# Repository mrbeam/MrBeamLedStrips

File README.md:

# MrBeamLedStrips

MrBeamLedStrips is a standalone component that handles Mr Beam II's LED strips.

## Usage
#### Socket Connection
There is a socket: `/var/run/mrbeam_ledstrips.sock`

Currently MrBeamPlugin does not use the socket connection. 
Still this needs to be done for performance! Some day...

#### Command Line Interface (CLI)
Or use the command line interface:
* `mrbeam_ledstrips_cli [command]`  Commands:

    * `` (no command) Prints version of MrBeamLedStrips. (Does not connect to daemon.)
    * `?` Prints version, list of possible commands and debug information
    * `unknown`
    * `DebugStop`  # breaks -> SW-1733
    * `on`, `all_on`
    * `off`, `all_off`
    * `brightness` # Error
    * `rollback`
    * `fps` # Error
    * `spread_spectrum` # Error
    * `ignore_next_command`
    * `ignore_stop`
    * `Listening`, `_listening`, `listening`
    * `Startup`
    * `ClientOpened`
    * `ClientClosed`
    * `Error`
    * `Shutdown`
    * `ShutdownPrepare`
    * `ShutdownPrepareCancel`
    * `Upload`
    * `PrintStarted`
    * `PrintDone`
    * `PrintCancelled`
    * `PrintPaused`
    * `PrintPausedTimeout`
    * `PrintPausedTimeoutBlock`
    * `ButtonPressReject`
    * `PrintResumed`
    * `Progress:<progress>`, `progress:<progress>`
    * `JobFinished`, `job_finished`
    * `Pause`, `pause`
    * `ReadyToPrint`
    * `ReadyToPrintCancel`
    * `SlicingStarted`
    * `SlicingDone`
    * `SlicingCancelled`
    * `SlicingFailed`
    * `SlicingProgress:<progress>`, `slicing_progress:<progress>`
    * `SettingsUpdated`  # breaks -> SW-1733
    * `LaserJobDone`
    * `LaserJobCancelled`
    * `LaserJobFailed`
    * `white`, `all_white`
    * `red`, `all_red`
    * `green`, `all_green`
    * `blue`, `all_blue`
    * `yellow`, `all_yellow`
    * `orange`, `all_orange`

## Config
For configuration see:
 * `iobeam/extras/mrbeam_ledstrips.yaml` or 
 * `/etc/mrbeam_ledstrips.yaml` after deployment.

## Change Log

##### 0.1.11
New commands:
* Command `ButtonPressReject`: Intended to give feedback that a button press is an invalid action at the moment. 
Flashes red once and the rolls back.
* README.md added
##### < 0.1.10
See commit log

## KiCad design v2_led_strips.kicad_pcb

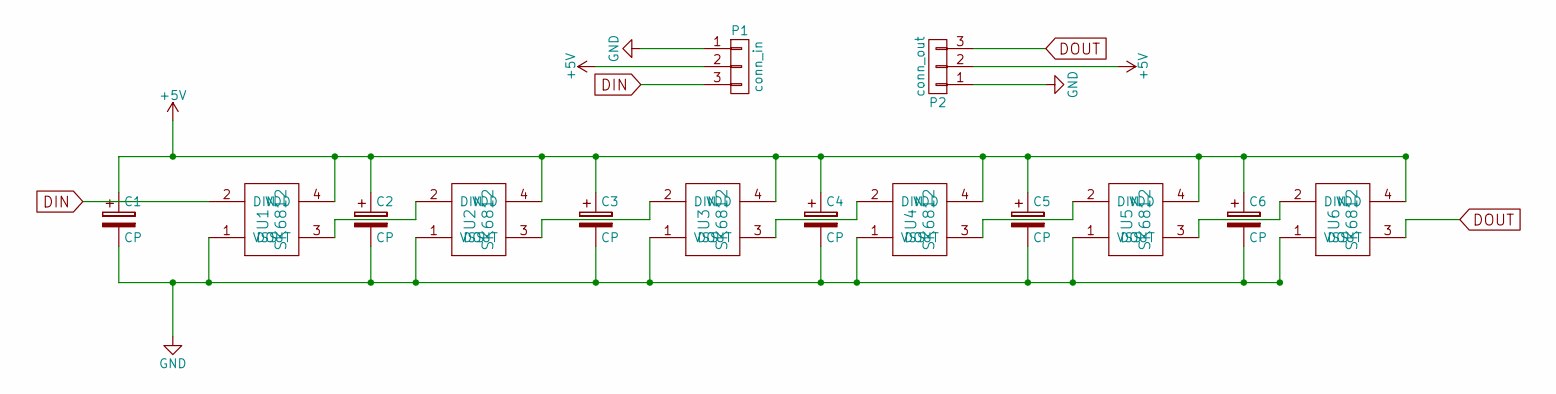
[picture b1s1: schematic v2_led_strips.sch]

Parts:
C1, C2, C3, C4, C5, C6: CP; C_1206
P1: conn_in; GS3
P2: conn_out; GS3
U1, U2, U3, U4, U5, U6: SK6812; PLCC4-5050

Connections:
+5V: C1.1, C2.1, C3.1, C4.1, C5.1, C6.1, P1.2, P2.2, U1.4 (VDD), U2.4 (VDD), U3.4 (VDD), U4.4 (VDD), U5.4 (VDD), U6.4 (VDD)
DIN: P1.3, U1.2 (DIN)
DOUT: P2.3, U6.3 (DOUT)
GND: C1.2, C2.2, C3.2, C4.2, C5.2, C6.2, P1.1, P2.1, U1.1 (VSS), U2.1 (VSS), U3.1 (VSS), U4.1 (VSS), U5.1 (VSS), U6.1 (VSS)
unnamed: U1.3 (DOUT), U2.2 (DIN)
unnamed: U2.3 (DOUT), U3.2 (DIN)
unnamed: U3.3 (DOUT), U4.2 (DIN)
unnamed: U4.3 (DOUT), U5.2 (DIN)
unnamed: U5.3 (DOUT), U6.2 (DIN)

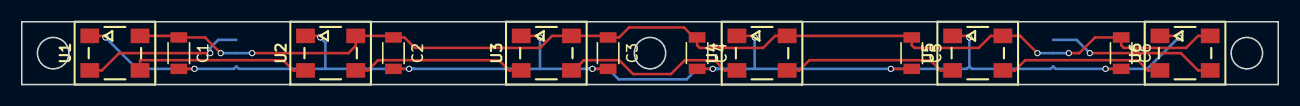
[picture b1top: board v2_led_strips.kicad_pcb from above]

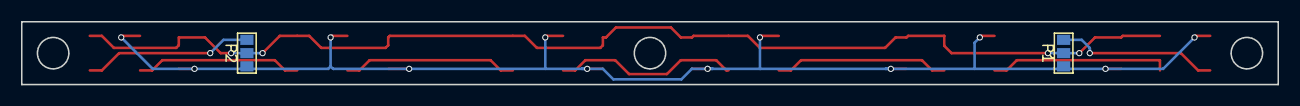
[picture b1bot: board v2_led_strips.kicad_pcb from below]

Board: 2 copper layers, 120.0 x 6.0 mm, 14 parts (2 on the bottom side), 9 nets.

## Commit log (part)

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2016-05-30 initial commit v2 led strips. work in progress.
2016-09-07 reusing this repo for LEDs software dev. initial commit
2016-09-07 added src folder
2016-09-07 color definitions
2016-09-07 fixed progress 100% value
2016-09-07 reading state from socket
2016-09-08 work in progress
2016-09-09 bugfix.
2016-09-09 added ws281x lib
2016-09-10 cli for chatting with socket
2016-09-10 wip: added installer
2016-09-10 move did not work.
2016-09-10 renamed package
2016-09-10 package init file and versioneer file
2016-09-10 import fixes
2016-09-10 cleaner structure
2016-09-10 removed rpi_ws281x code as there is already a python package
2016-09-10 added config exception
2016-09-10 fetch config from file
2016-09-10 fixed imports
2016-09-10 better fail messages
2016-09-10 pid-file is handled by daemon - not by init script.
2016-09-11 added unit file for systemd based distributions
2016-09-19 slower clientOpened connection
2016-10-10 added all_on state for power measurements
2016-10-10 fixed indentation
2016-10-20 bugfix. indentations.
2016-10-20 bugfix - unit files have extension .service
2017-01-12 added pycharm project folder to to .gitignore
2017-01-13 fixed spacing
2017-01-13 fixed a lot of spacing and semicolon stuff
2017-01-17 initial commit of update bash script.
2017-01-17 added uninstall and install to update script.
2017-01-17 fixed naming error.
2017-01-17 added "don't ask for confirmation" option to uninstall command
2017-01-23 added line to test software update.
2017-01-23 fixed typo in systemctl restart command.
2017-01-30 cleanup
2017-01-31 removed old SysV init script due to new systemd unit file.
2017-01-31 added copytruncate option to allow mrbeam_ledstripes to always write to the same file. This solves the empty log file bug.
2017-01-31 removed config file for SysV init script.
2017-02-01 removed copy line of previous deleted config file.
2017-03-31 removed some optional arguments which allows us to use the pip installed rpi-ws281x package without the special scons install and such.
2017-03-31 removed the dependency link to the forked repo because we can easily use the original one.
2017-04-07 changed from the 2x4 inside led strips to the 1x18 led strip.
2017-04-07 revert the execstart path again.
2017-04-11 Client returns version if called without arguments.
2017-04-11 added debug static single colors RGB.
2017-04-11 fixed wrong led count. 46 instead of 36.
2017-04-11 fixed wrong colors. Check why they are now changed.
2017-04-11 fixed led numbering error due to change of inside leds.
2017-04-11 rechanged the led colors again because on the new EMV device they are now wrong. Maybe this is an issue due to the diffrent pi ws281x libs.
2017-04-13 clean up.
2017-04-18 Added shutdown animations (Shutdown and ShutdownPrepare)
2017-04-20 implemented rollback and ShutdownPrepareCancel
2017-04-25 new states: ReadyToPrint, ReadyToPrintCancel. Fixed rollback
2017-05-02 Fixed a typo that caused a crash and added a logline
2017-05-02 fixed another half-assed refactoring that caused a bug.
2017-05-12 ShudownPrepare starts with brighter red
2017-06-02 added fps feature and lazy updates
2017-06-02 debug logging
2017-06-02 bugfix
2017-06-02 more logging
2017-06-07 Now running with 28fps, all animations fixed
2017-06-07 Slowed down Slicing states
2017-06-09 Adjustable FPS, spread_spectrum, constants moved to config file
2017-06-09 Added spread_spectrum_random config
2017-06-14 removed rpi_ws281x dependency because it will be installed from our own fork manually inside OctoPi.
2017-06-14 Fixed a config bug and added a try-catch
2017-06-14 Default configuration
2017-06-14 Removed intentional crash for debugging purpose... (emberassing...)
2017-06-28 Server now responds with a real OK/Error message, introduced info command, accidentally reformatted server.py
2017-06-28 Reorganized states in dict
2017-06-28 Added MrBeam strip type. (Don't leave it to the NeoPixel defaults...)
2017-06-28 Added DebugStop
2017-06-28 Handles SIGUSR1 for debugging...
2017-07-10 fixed TypeError: threshold = value / 100.0 * (l-1) TypeError: unsupported operand type(s) for /: 'str' and 'float'
2017-07-11 finaly fixed TypeError: threshold = value / 100.0 * (l-1) TypeError: unsupported operand type(s) for /: 'str' and 'float' by forcing an integer conversion on "value".
2017-07-21 fixed error when fade_off was called and all leds are turned off, but the inside leds should not been turned off.
2017-07-24 fixed global brightness setting bug which also dimmed the interior leds.
2017-07-24 fixed wrong led color read.
2017-07-24 added mylinspace function to calculate fixed step size list of brightness.
2017-08-01 initial commit of new laser event changes.
2017-08-07 v0.1.5 switch from versioneer to manual versions
2017-08-07 added version to info output
2017-08-08 added commands for orange and yellow
2017-08-08 flash commands and bug fixes
2017-08-24 v.0.1.6: introduced color white, flashing colors and several new commands for mrb_check
2017-08-25 removed try/catch that did more bad than good. and typo
2017-09-08 changed default dma channel to 10 which resolves the read only mounted sd card problem.
2017-09-08 removed multi-user.target from after to run very early.
2017-09-11 added comment with link to the problem.
2017-09-15 do gamma correction and end of line directly before setting the value.
2017-09-15 changed version to 0.1.7
2017-10-12 v0.1.8: supports ignore_next_command for self test
2017-10-20 v0.1.9 added inrgnore_stop
2017-11-02 0.1.10 fixed: ignore_stop returned ERROR output instead of OK
2017-11-22 v0.1.11: Introducing 'ButtonPressReject' and README.md
2018-01-19 v0.1.12: progress command takes floats as well. This is because we're about to change this in MrBeamPlugin likely to com in plugin version 0.1.21 or 0.1.22
2018-06-08 added support for our focus tool
2018-06-08 added S for skip, N for OFF and changed default behaviour to OFF if parameter unknown
2018-06-08 dimmed focus tool colors.
2018-10-12 v0.1.13: PrintDone changes to WHITE from ORANGE - state progress is no longer reset if same state is requested twice. - threading.lock in change_state() method
2019-01-25 introducing static breathing
2019-01-25 bug: UNKNOWN state was not handled
2019-01-28 some cleanup
2019-02-08 introducing three color breathing
2019-02-11 default listening state adapted to OP syntax, breathing_static has an optional fade-in
2019-02-19 adding analytics module...
2019-04-01 Added exception-hook, fixed issue with caller-key.
2019-04-01 v0.1.16: bumping version
2019-04-04 bugfixes in analytics
2019-04-27 first draft of png animations
2019-04-27 png animations. works first time.
2019-11-12 0.1.17
2020-01-07 shutdown improvements.
2020-01-16 v0.1.18
2020-01-16 v0.1.18 (#7)
    * shutdown improvements.
    * v0.1.18
2020-01-22 0.1.19: Introducing set: command to set settings like brightness
2020-01-23 fix. inside brightness works now as well.
2020-05-19 0.1.20: Introducing duration param for color: and flash_color: commands
2020-05-30 new command 'lens_calibration', static_color now has optional inside color parameter
2020-05-30 optimized inner brightness
2020-06-03 0.1.21: Added duration param for lens_calibration command
2020-06-12 v0.1.22: Added blink_color, blint_green, blink_red,... legacy command upload still works and accepts rgb params like 'upload:0:255:0'
2020-08-10 v0.1.24: Fixed minor bug in analytics: "Unknown state: rollback"
2020-09-09 Set interior lights to full (most) brightness for lens calibration.
2020-09-09 v0.1.25
2020-09-15 v0.1.26: Removed interior dim for lens calibration
2020-10-08 fix typo in README
2021-02-27 Deactivate analytics by default.
2021-02-27 Bump version.
2021-02-27 Fix py2 absolute import.
2021-03-08 Fix default config.
2021-03-08 Fix indentation.
2021-03-08 Fix import.
2021-03-09 Single packet communication.
    Reduces trickery to fix bad communication handling with sendall and
    recv.
    Also, code becomes py2 incompatible (with using str to decode utf8)
2021-03-09 Rm unnecessary packet sent
2021-03-24 2to3.
2021-03-24 absolute import.
2021-03-31 Enable analytics by default.
2021-04-07 Fix setup.py to have pip 9
    Only pip 9.x compatible for python2.
2021-04-12 Remove comment.
2021-04-15 Fix sys import in the setup.py file
2021-04-19 Fix client server communication for py2 version.
2021-04-19 Bumps version.
2021-05-10 Fix missing analytics import
2021-05-10 Fixed undefined var
2021-07-15 SW-153 bump version
2021-10-12 Refactor/Split responsabilities and add tests
    - Split the cli parsing and handling (at least partially)
    - Set the default color set in an Enum
    - sort imports
    - state history is a self-limiting buffer
    - Add a `stop()` function to gracefully end the handling loop
    - Remove unnecessary comments
2021-10-12 Refactor/Separate settings from other commands
    - Parse settings from the same function as the Command parser
    - Raise an Exception that wasn't handled in the socket monitoring loop
2021-10-12 Refactor/Sleep for a frame in the handle function.
2021-10-12 Fix+Refactor/Add COMMANDS_REQ_ARG
    - Forgot to add the list of commnads that require at least an argument
    - Refactor the list of LED IDs with a readable range()
2021-10-12 Remove unused focus tool colors
2021-10-12 Remove all focus tool logic (unused)
2021-10-12 Fix rollback bug.
    - Adds tests fr the rollback method.
2021-10-12 Fix rollback bug
    Add tests to verify rollback stability
2021-10-12 Add docstrings
    - rm commented code
    - fewer code repeats.
2021-10-13 Remove 'enum' as a dependency
    I didn't figure it was a built-in lib.
2021-10-13 Add docstrings.
2021-10-13 Refactor/Move basic functions out of LED class.
2021-10-13 Fix _my_linspace.
2021-10-13 Fixes/Various
    - Add opencv as a requirement (limited to py3)
    - Fix dimming color when given an enum instead of int
    - Fix rollback test as it didn't initialise state array correctly
    - Fix undefined `fps` var
2021-10-13 Doc+Refactor/Various
    - Use Constant OUTSIDE_LEDS instead of defining `involved_registers`
    every time.
    - logger.warn() ==> logger.warning() (Deprecation warnings)
    - use reversed(range(N)) instead of range(N-1, -1, -1)
    - `for i in range(len(my_list))` ==> `for i, elm in enumerate(my_list)`
    - `Colors.OFF if brightness==0 else dim_color(my_color, brightness)`
2021-10-13 Set fps to minimum 1 Hz.
2021-10-13 Refactor/Various
    - move repeated complex formula into function
    - mute unused variable
    - progress_pause() uses progress() instead of copy-pasta
2021-10-13 Fix breath factor.
2021-10-13 Refactor/range() -> enumerate() refactors.
2021-10-13 Refactor/Pytest cleanup.
2022-03-23 update versioneer reformat setup.py file
2022-03-24 https://github.com/mrbeam/MrBeamLedStrips/pull/33#discussion_r833991473
2022-03-24 https://github.com/mrbeam/MrBeamLedStrips/pull/33#discussion_r833987534
2022-03-25 SW-1152-update-ledstrips-versioneer (#33)
    * update versioneer
    * reformat setup.py file
2022-08-25 Add python version to setup.py
2022-08-25 Remove double parenthesis from prints
2022-08-25 Add comments to readme
2022-08-25 Remove Python2 support
2022-08-29 SW-1398 led strips to python 3.10.6 (#36)
    * Add python version to setup.py
    * Remove double parenthesis from prints
    * Add comments to readme
    * Remove Python2 support
2023-08-09 Update service file for new installation path
2023-08-11 Import pkg_resources package when it is needed
2023-08-11 replace deprecated pkg_resources and fix use of version
2023-08-11 try to fix cli usage
2023-08-29 SW-3820 Handle some minor errors in ledstrips * Use 2 trailing _ for version * Set right path for octoprint executable * Implement temporary fix for laserjob progress.(handle properly in SW-3799).
2023-08-29 SW-3820 formatting changes
